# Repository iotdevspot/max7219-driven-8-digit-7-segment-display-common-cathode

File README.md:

# max7219-driven-8-digit-7-segment-display-common-cathode
This is my first PCB that got manufactured A display driver module with Maxim's MAX7219CNG IC and two four digit seven segment displays. The design was made with Eagle and it was manufactured by JLCPCB.

The repository contains Arduino example codes, images of the PCBs and of the assembled module, Eagle schematic and board layout and gerber files. Some of the components are still missing from the 3D model so it's unavailable yet, but I'll upload to my Fusion360 [gallery](https://gallery.autodesk.com/fusion360/users/S2YAKSQZSPKT) as it's ready.

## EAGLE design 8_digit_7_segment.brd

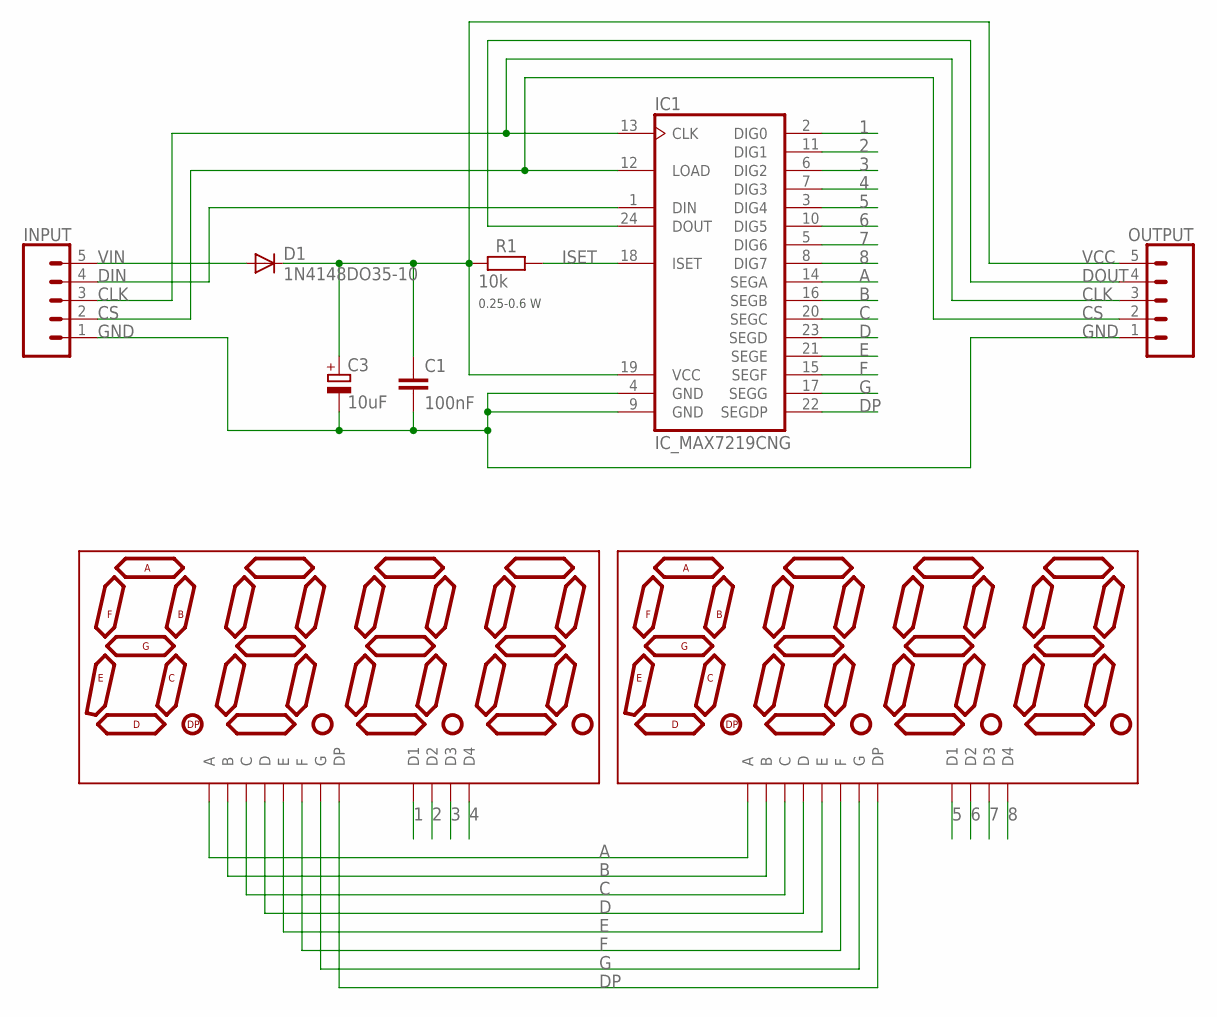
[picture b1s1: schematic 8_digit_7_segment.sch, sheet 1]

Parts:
C1: 100nF; C025-024X044
C3: 10uF; E2-5
D1: 1N4148DO35-10; D-10
DISP5, DISP6: ATA8041ARBJ; 7-SEGMENT-4DIGIT-20MM
IC1: IC_MAX7219CNG; DIL24-3
INPUT: CONN_051X05LA; 1X05/90
OUTPUT: CONN_051X05/90_FEMALE; 1X05/90FEMALE
R1: 10k; 0207/7

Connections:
1: DISP5.12 (D1), IC1.2 (DIG0)
2: DISP5.9 (D2), IC1.11 (DIG1)
3: DISP5.8 (D3), IC1.6 (DIG2)
4: DISP5.6 (D4), IC1.7 (DIG3)
5: DISP6.12 (D1), IC1.3 (DIG4)
6: DISP6.9 (D2), IC1.10 (DIG5)
7: DISP6.8 (D3), IC1.5 (DIG6)
8: DISP6.6 (D4), IC1.8 (DIG7)
A: DISP5.11 (A), DISP6.11 (A), IC1.14 (SEGA)
B: DISP5.7 (B), DISP6.7 (B), IC1.16 (SEGB)
C: DISP5.4 (C), DISP6.4 (C), IC1.20 (SEGC)
CLK: IC1.13 (CLK), INPUT.3, OUTPUT.3
CS: IC1.12 (LOAD), INPUT.2, OUTPUT.2
D: DISP5.2 (D), DISP6.2 (D), IC1.23 (SEGD)
DIN: IC1.1 (DIN), INPUT.4
DOUT: IC1.24 (DOUT), OUTPUT.4
DP: DISP5.3 (DP), DISP6.3 (DP), IC1.22 (SEGDP)
E: DISP5.1 (E), DISP6.1 (E), IC1.21 (SEGE)
F: DISP5.10 (F), DISP6.10 (F), IC1.15 (SEGF)
G: DISP5.5 (G), DISP6.5 (G), IC1.17 (SEGG)
GND: C1.2, C3.-, IC1.4 (GND), IC1.9 (GND), INPUT.1, OUTPUT.1
ISET: IC1.18 (ISET), R1.2
VCC: C1.1, C3.+, D1.C, IC1.19 (VCC), OUTPUT.5, R1.1
VIN: D1.A, INPUT.5

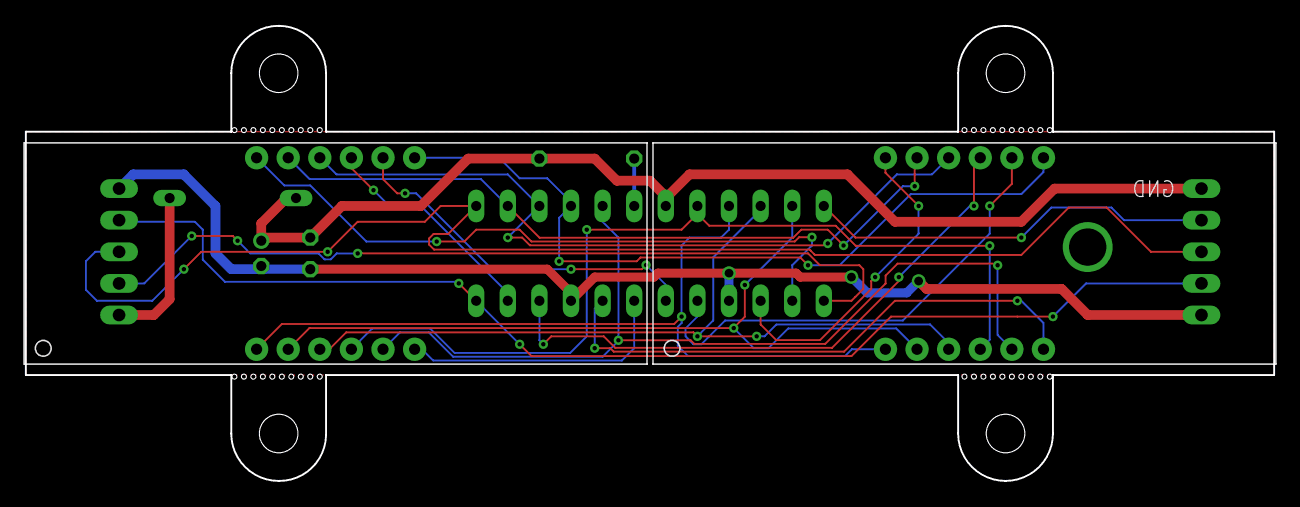
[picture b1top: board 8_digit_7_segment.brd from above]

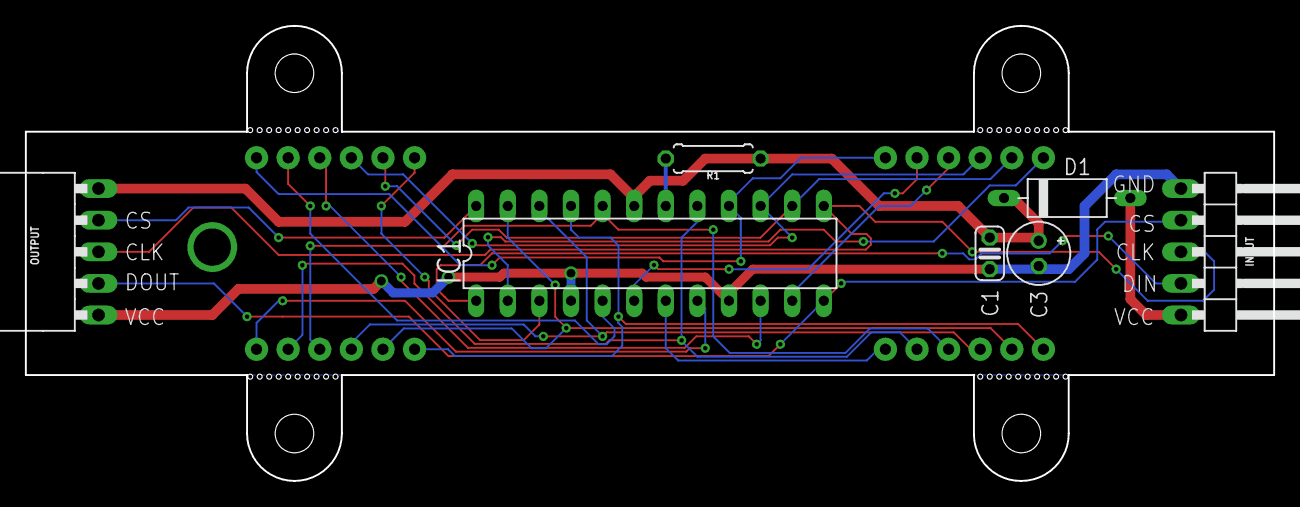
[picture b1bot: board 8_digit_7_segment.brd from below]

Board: 2 copper layers, 100.3 x 36.6 mm, 9 parts (7 on the bottom side), 24 nets.

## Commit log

2018-10-05 Eagle files and two arduino test sketch added
2018-10-09 Minor modifications, 3D components added to the Eagle files and new images added of the 3D model
2018-10-12 STEP file (3D model of the module) and slight modification after manufacturing
